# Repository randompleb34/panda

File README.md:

# PANDA R1 Flight Computer
Precision Altimeter and Nano Development Arduino. A custom ESP-32 based microcontroller with integrated altimeter and battery management system. Allows for  modular stackable hats for additional instrument clusters.

## Documentation
The files provided above includes the necessary files to fabricate the PCB for KiCad 8.0 and above. A bill of materials is also included for Mouser Electronics.

## Specs
The complete specs are avaliable at michaelsongdesign.com/projects/panda

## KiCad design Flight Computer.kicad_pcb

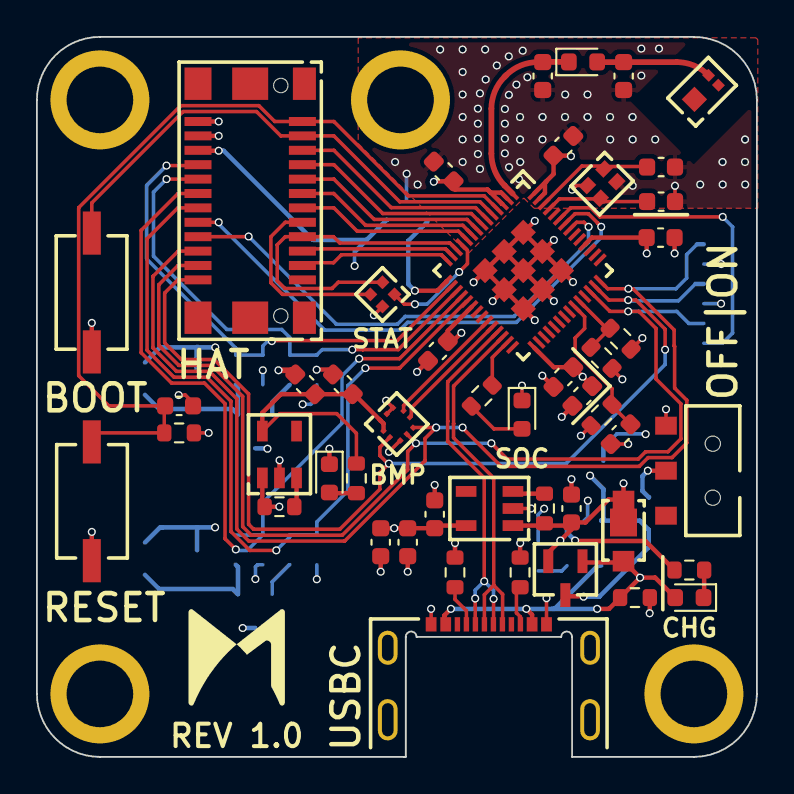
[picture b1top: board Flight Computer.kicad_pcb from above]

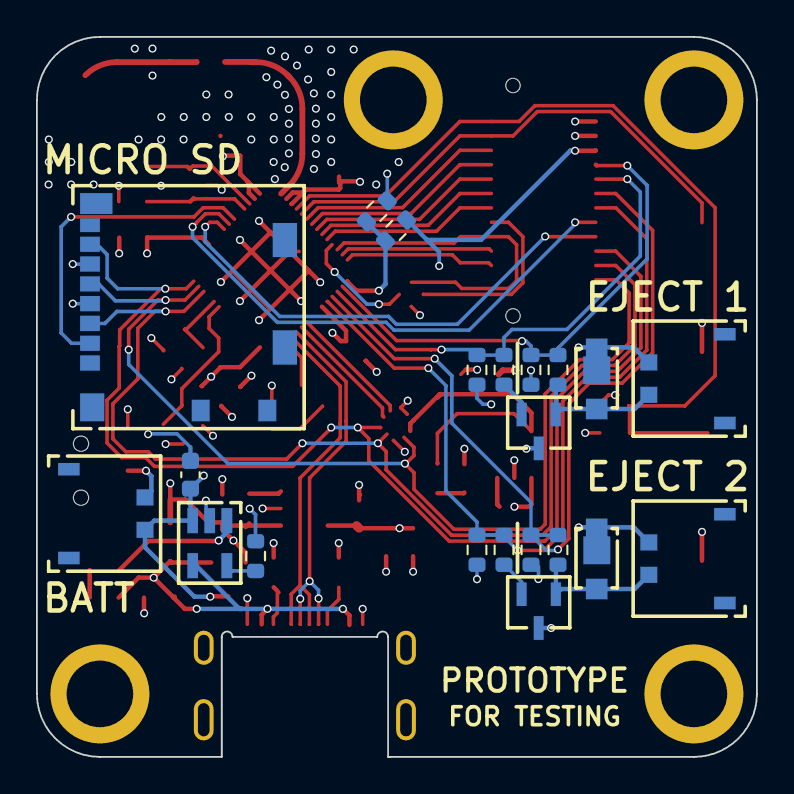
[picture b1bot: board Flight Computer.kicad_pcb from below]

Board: 4 copper layers, 40.0 x 40.0 mm, 69 parts (21 on the bottom side), 54 nets.

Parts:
390: BMP390; 10LGA_2X2X0p75_BOS
ANT: NN01-102; XCVR_NN02-101
BATT: EZ; 2082940020
BMP: GREEN; LED_0603_1608Metric
BOOT: Switch; PTS636SK25FSMTRLFS
C1, C2, C3, C5, C17, C19: 10uF; C_0603_1608Metric
C6, C15, C18: 0.1uF; C_0603_1608Metric
C7, C8, C9, C16: 1uF; C_0603_1608Metric
C10: 1.2pF; C_0603_1608Metric
C11, C12: 10pF; C_0603_1608Metric
C13: 1.8pF; C_0603_1608Metric
CAP: 0.1uF; C_0603_1608Metric
CAP#2: 10K; R_0603_1608Metric
CAP#3: 0.1uF; C_0603_1608Metric
CHG: ORANGE; LED_0603_1608Metric
D1, D4, D5: CDBC540-HF; PMEG4010EXEX
EJECT 1, EJECT 2: EZ; 2082940020
HAT: 1775013-2; 17750132
IC1: MCP73831T-2ACI_OT; SOT95P270X145-5N
IC2, IC3: AP2112K-3.3TRG1; SOT95P285X140-5N
L1: 2.4nH; D_0603_1608Metric
MICRO SD: Micro_SD_Card_Det1; microSD_HC_Molex_104031-0811
OFF|ON: ON/OFF; AYZ0102AURLC
Q2, Q3: DMN3042L-7; SOT-23_DIO
R1, R2, R10: 100K; R_0603_1608Metric
R3: 442K; R_0603_1608Metric
R4: 160K; R_0603_1608Metric
R5, R8, R9, R19, R20: 5.1K; R_0603_1608Metric
R7, R11, R12, R14, R18: 10K; R_0603_1608Metric
R13, R15: 1K; R_0603_1608Metric
R16, R17: 100; R_0603_1608Metric
R21: 3.3K; R_0603_1608Metric
R23: 442k; R_0603_1608Metric
RESET: Switch; PTS636SK25FSMTRLFS
SEN: 2K; R_0603_1608Metric
SOC: RED; LED_0603_1608Metric
STAT: IN-PI15TAT5R5G5B; INPI15TAT5R5G5B
U3: DMP2045U-7; SOT-23_DIO
U5: ESP32-S3FH4R2; QFN40P700X700X90-57N
USBC: 2169900003; MOLEX_2169900003
XTAL: 830108208709; ABM11

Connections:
+3.3V: C2.1, C3.1, C5.1, C6.1, C8.1, C15.1, C16.1, CAP.1, CAP#2.1, CAP#3.1, HAT.14, IC2.5 (VOUT), MICRO SD.4 (VDD), U5.2 (VDD3P3), U5.3 (VDD3P3), U5.20 (VDD3P3_RTC), U5.29 (VDD_SPI), U5.46 (VDD3P3_CPU), U5.55 (VDDA), U5.56 (VDDA)
+BATT: BATT.2, C19.1, HAT.15, IC1.3 (VBAT), R3.2, U3.3
/VOUT: 390.1 (VDDIO), 390.10 (VDD), C17.1, C18.1, IC3.5 (VOUT), R11.1
D+: U5.26 (GPIO20), USBC.A6 (DP1), USBC.B6 (DP2)
D-: U5.25 (GPIO19), USBC.A7 (DN1), USBC.B7 (DN2)
GND: 390.3 (VSS), 390.8 (VSS), 390.9 (VSS), BMP.1 (K), BOOT.2 (NO), C1.2, C2.2, C3.2, C5.2, C6.2, C7.1, C8.2, C9.2, C10.1, C11.1, C12.1, C13.1, C15.2, C16.2, C17.2, C18.2, C19.2, CAP.2, CAP#3.2, HAT.13, IC1.2 (VSS), IC2.2 (GND), IC3.2 (GND), MICRO SD.6 (VSS), OFF|ON.3 (NO), Q2.3 (S), Q3.3 (S), R1.2, R4.1, R7.2, R8.1, R9.2, R12.2, R14.2, R18.2, R20.2, R23.1, RESET.1 (COM), SEN.1, SOC.1 (K), STAT.4 (GND), U5.57 (GND), USBC.A1_B12 (GND), USBC.B1_A12 (GND__1), XTAL.2 (GND_1), XTAL.4 (GND_2)
IO0: BOOT.1 (COM), HAT.2, U5.5 (GPIO0)
IO1: HAT.3, U5.6 (GPIO1)
IO2: HAT.4, U5.7 (GPIO2)
IO3: HAT.5, U5.8 (GPIO3)
IO4: HAT.6, U5.9 (GPIO4)
IO5: HAT.7, U5.10 (GPIO5)
IO6: STAT.1 (DIN), U5.11 (GPIO6)
IO7: HAT.9, STAT.2 (VDD), U5.12 (GPIO7)
IO10: R3.1, R4.2, U5.15 (GPIO10)
IO11: HAT.16, R13.1, R14.1, U5.16 (GPIO11)
IO12: HAT.17, R17.2, R18.1, U5.17 (GPIO12)
IO13: HAT.18, R12.1, R15.1, U5.18 (GPIO13)
IO14: HAT.19, R7.1, R16.2, U5.19 (GPIO14)
IO17: 390.7 (INT), U5.23 (GPIO17)
IO18: 390.6 (CSB), U5.24 (GPIO18)
IO21: R5.2, U5.27 (GPIO21)
IO33: R21.1, SEN.2, U5.38 (GPIO33)
IO45: MICRO SD.2 (DAT3/CD), U5.51 (GPIO45)
LED_OUT: HAT.8, STAT.3 (DOUT)
LNA_IN: C13.2, L1.1, U5.1 (LNA_IN)
MISO: 390.5 (SDO), HAT.22, MICRO SD.7 (DAT0), U5.42 (GPIO37)
MOSI: 390.4 (SDI), HAT.23, MICRO SD.3 (CMD), U5.40 (GPIO35)
unnamed: ANT.1, C10.2, L1.2
unnamed: CHG.1 (K), R19.2
unnamed: R5.1, SOC.2 (A)
unnamed: BMP.2 (A), R11.2
unnamed: D4.2 (A), EJECT 1.1, Q2.1 (D), R13.2
unnamed: D5.2 (A), EJECT 2.1, Q3.1 (D), R15.2
unnamed: IC1.5 (PROG), R20.1
unnamed: IC1.1 (STAT), R19.1
unnamed: IC2.3 (EN), R2.1
unnamed: IC3.3 (EN), R10.2
unnamed: BATT.1, OFF|ON.2 (COM)
unnamed: R8.2, USBC.A5 (CC1)
unnamed: R9.1, USBC.B5 (CC2)
unnamed: Q2.2 (G), R17.1
unnamed: Q3.2 (G), R16.1
RESET: C9.1, CAP#2.2, HAT.1, RESET.2 (NO), U5.4 (CHIP_PU)
RX: HAT.20, U5.50 (GPIO44/U0RXD)
SCK: 390.2 (SCK), HAT.24, MICRO SD.5 (CLK), U5.41 (GPIO36)
SCL: HAT.11, U5.14 (GPIO9)
SDA: HAT.10, U5.13 (GPIO8)
SPICLK_P: C7.2, R23.2, U5.37 (GPIO47/SPICLK_P)
TX: HAT.21, U5.49 (GPIO43/U0TXD)
VBUS: CHG.2 (A), D1.2 (A), IC1.4 (VDD), R1.1, R21.2, U3.1, USBC.A4_B9 (VBUS), USBC.B4_A9 (VBUS__1)
VHI: C1.1, D1.1 (K), D4.1 (K), D5.1 (K), EJECT 1.2, EJECT 2.2, IC2.1 (VIN), IC3.1 (VIN), R2.2, R10.1, U3.2
XTAL_N: C11.2, U5.53 (XTAL_N), XTAL.3 (CRYSTAL_2)
XTAL_P: C12.2, U5.54 (XTAL_P), XTAL.1 (CRYSTAL_1)

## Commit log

2025-01-20 Create LICENSE
